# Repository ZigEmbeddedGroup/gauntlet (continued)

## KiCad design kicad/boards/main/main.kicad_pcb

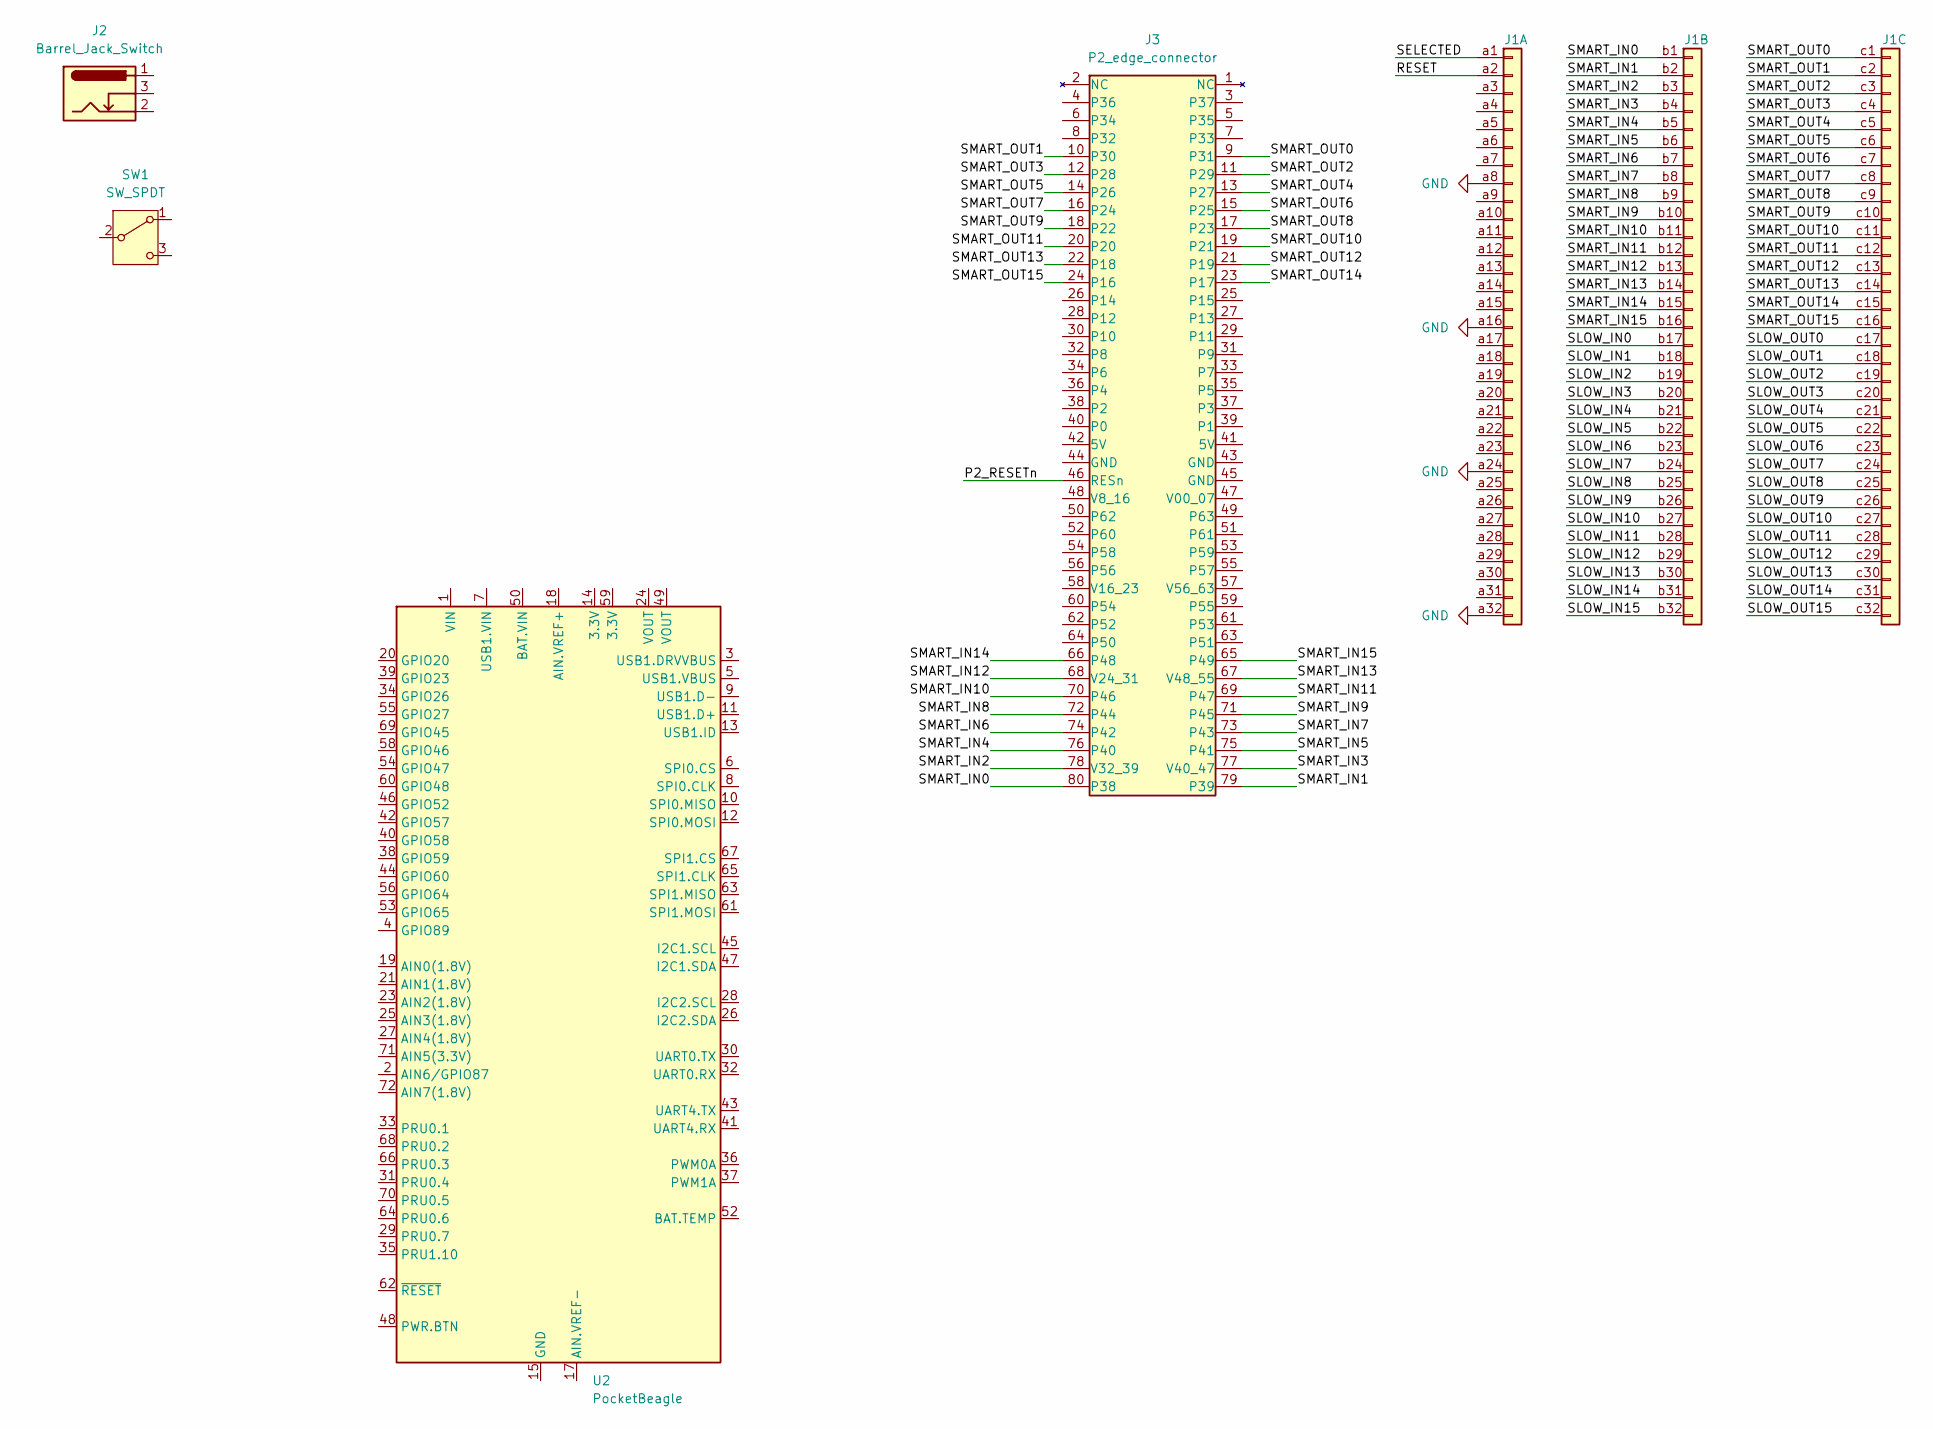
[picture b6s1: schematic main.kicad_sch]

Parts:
J1: DIN41612_03x32_C_Split; DIN41612_C_3x32_Male_Horizontal_THT
J2: Barrel_Jack_Switch; QFN-40-1EP_6x6mm_P0.5mm_EP4.6x4.6mm
J3: P2_edge_connector; 4UCON_10156_2x40_P1.27mm_Socket_Horizontal
SW1: SW_SPDT; SW_NKK_GW12LJP
U2: PocketBeagle; BeagleBoard_PocketBeagle

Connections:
/P2_RESETn: J3.46 (RESn)
/RESET: J1.a2
/SELECTED: J1.a1
/SLOW_IN0: J1.b17
/SLOW_IN1: J1.b18
/SLOW_IN2: J1.b19
/SLOW_IN3: J1.b20
/SLOW_IN4: J1.b21
/SLOW_IN5: J1.b22
/SLOW_IN6: J1.b23
/SLOW_IN7: J1.b24
/SLOW_IN8: J1.b25
/SLOW_IN9: J1.b26
/SLOW_IN10: J1.b27
/SLOW_IN11: J1.b28
/SLOW_IN12: J1.b29
/SLOW_IN13: J1.b30
/SLOW_IN14: J1.b31
/SLOW_IN15: J1.b32
/SLOW_OUT0: J1.c17
/SLOW_OUT1: J1.c18
/SLOW_OUT2: J1.c19
/SLOW_OUT3: J1.c20
/SLOW_OUT4: J1.c21
/SLOW_OUT5: J1.c22
/SLOW_OUT6: J1.c23
/SLOW_OUT7: J1.c24
/SLOW_OUT8: J1.c25
/SLOW_OUT9: J1.c26
/SLOW_OUT10: J1.c27
/SLOW_OUT11: J1.c28
/SLOW_OUT12: J1.c29
/SLOW_OUT13: J1.c30
/SLOW_OUT14: J1.c31
/SLOW_OUT15: J1.c32
/SMART_IN0: J1.b1, J3.80 (P38)
/SMART_IN1: J1.b2, J3.79 (P39)
/SMART_IN2: J1.b3, J3.78 (V32_39)
/SMART_IN3: J1.b4, J3.77 (V40_47)
/SMART_IN4: J1.b5, J3.76 (P40)
/SMART_IN5: J1.b6, J3.75 (P41)
/SMART_IN6: J1.b7, J3.74 (P42)
/SMART_IN7: J1.b8, J3.73 (P43)
/SMART_IN8: J1.b9, J3.72 (P44)
/SMART_IN9: J1.b10, J3.71 (P45)
/SMART_IN10: J1.b11, J3.70 (P46)
/SMART_IN11: J1.b12, J3.69 (P47)
/SMART_IN12: J1.b13, J3.68 (V24_31)
/SMART_IN13: J1.b14, J3.67 (V48_55)
/SMART_IN14: J1.b15, J3.66 (P48)
/SMART_IN15: J1.b16, J3.65 (P49)
/SMART_OUT0: J1.c1, J3.9 (P31)
/SMART_OUT1: J1.c2, J3.10 (P30)
/SMART_OUT2: J1.c3, J3.11 (P29)
/SMART_OUT3: J1.c4, J3.12 (P28)
/SMART_OUT4: J1.c5, J3.13 (P27)
/SMART_OUT5: J1.c6, J3.14 (P26)
/SMART_OUT6: J1.c7, J3.15 (P25)
/SMART_OUT7: J1.c8, J3.16 (P24)
/SMART_OUT8: J1.c9, J3.17 (P23)
/SMART_OUT9: J1.c10, J3.18 (P22)
/SMART_OUT10: J1.c11, J3.19 (P21)
/SMART_OUT11: J1.c12, J3.20
/SMART_OUT12: J1.c13, J3.21 (P19)
/SMART_OUT13: J1.c14, J3.22 (P18)
/SMART_OUT14: J1.c15, J3.23 (P17)
/SMART_OUT15: J1.c16, J3.24 (P16)
GND: J1.a8, J1.a16, J1.a24, J1.a32
unnamed: U2.15 (GND), U2.16 (GND), U2.22 (GND), U2.51 (GND), U2.57 (GND)

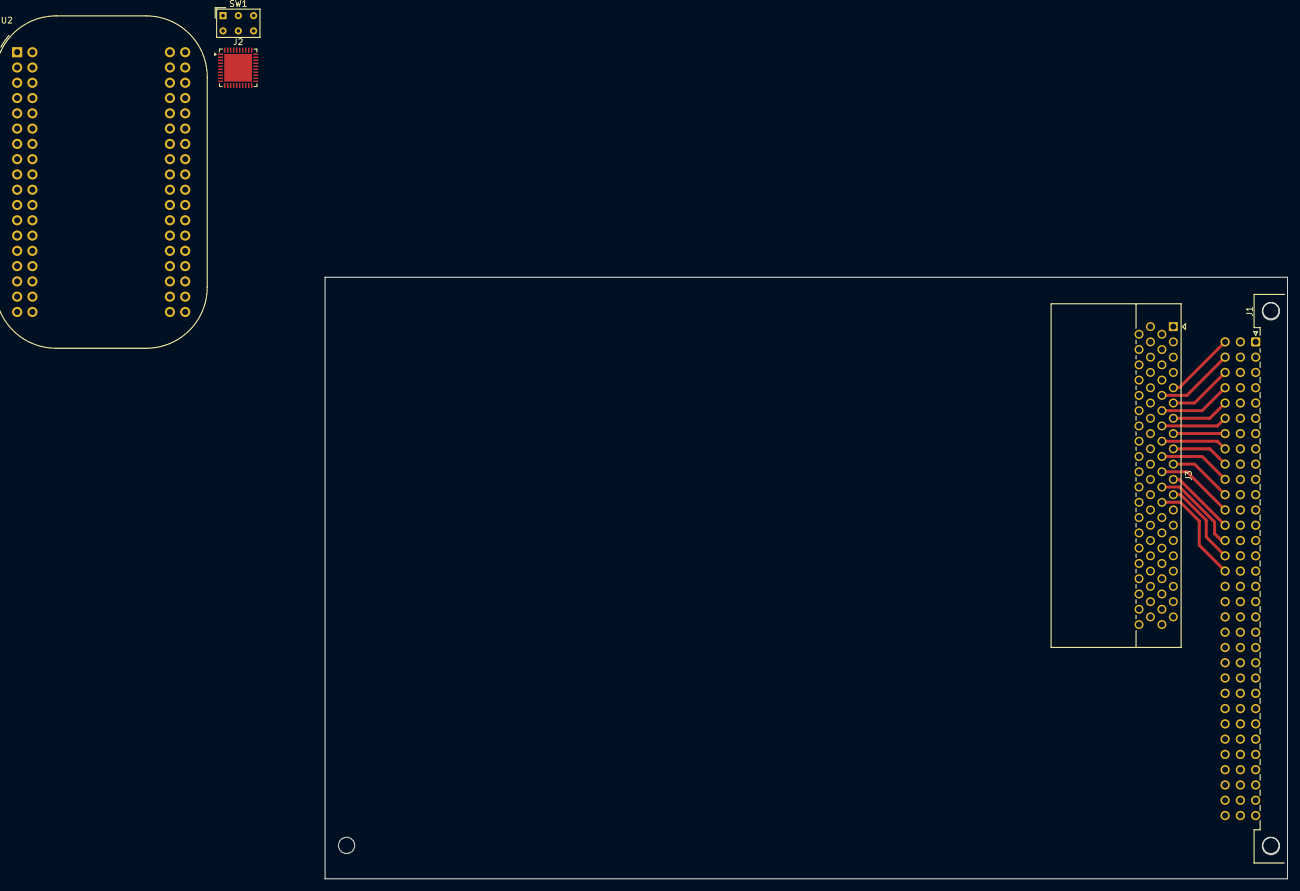
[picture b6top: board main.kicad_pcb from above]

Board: 2 copper layers, 160.0 x 100.0 mm, 8 parts (0 on the bottom side), 34 nets.

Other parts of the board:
MH2, MH3, MH4: MountingHole_2.7mm_M2.5_DIN965
